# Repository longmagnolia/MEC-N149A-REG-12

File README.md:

# Neumann N149A/V Tube Power Supply Reverse Engineering
This project aims to reverse engineer and document the design of Neumann type N194A and N194V power supplys.
Furthermore, this project is primarily concerned the deisgn of the PCB found inside as well as offering a replacement linear design for the discrete SMPS inside of each stock unit.

# Operation
These power supplys offer a small variety of voltage rails to be used with a connected Neumann M147, M149, or M150 type tube large diaphragm condensor microphone. 

The power supplys operate largely with main two blocks. First, being the discrete switch mode power supply often found to be a Globtek "TR9KE1250LCP-Y" or similar. These are typically a 12V 1.25A 15W black brick type SMPS used to step the incoming 120VAC from the wall down to 12VDC to be used by other circuitry. Second, the remainder of the power supply is comprised by a PCB manufactured likely by Neumann that takes the 12VDC from the SMPS and makes the necessary rails for the microphone. On this board the DIN-8 connector for linking to the microphone and XLR-3 connector for output are found.

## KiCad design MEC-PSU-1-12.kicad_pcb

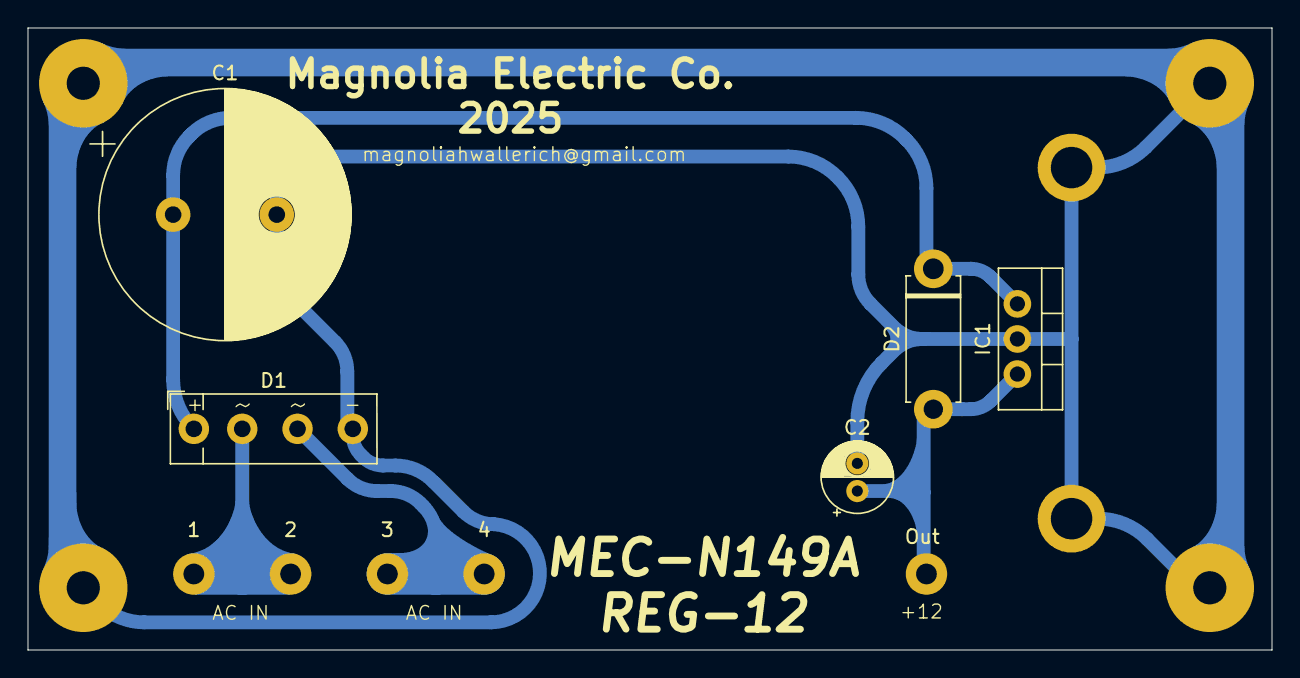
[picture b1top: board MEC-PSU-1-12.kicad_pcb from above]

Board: 2 copper layers, 90.0 x 45.0 mm, 11 parts (0 on the bottom side), 5 nets.

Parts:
1, 2, 3, 4: Conn_01x01_Socket; SolderWire-2.5sqmm_1x01_D2.4mm_OD4.4mm
C1: 2200µF 50V; CP_Radial_D18.0mm_P7.50mm
C2: 22µF 50V; CP_Radial_D5.0mm_P2.00mm
D1: KBP04G; Diode_Bridge_Vishay_KBPM
D2: 1N4004; D_5W_P10.16mm_Horizontal
Heatsink: Heatsink 35x13mm; Heatsink_Fischer_SK104-STCB_35x13mm__2xDrill3.5mm_ScrewM3
IC1: LM7812_TO220; TO-220-3_Vertical
Out: Conn_01x01_Socket; SolderWire-2.5sqmm_1x01_D2.4mm_OD4.4mm

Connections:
Earth: C1.2, C2.2, D1.2 (-), Heatsink.1, IC1.2 (GND)
unnamed: C1.1, D1.1 (+), D2.1 (K), IC1.1 (VI)
unnamed: C2.1, D2.2 (A), IC1.3 (VO), Out.1
unnamed: 1.1, 2.1, D1.3
unnamed: 3.1, 4.1, D1.4

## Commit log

2025-04-15 Adding schema & pcb files
2025-04-15 adding gbr & drl files
